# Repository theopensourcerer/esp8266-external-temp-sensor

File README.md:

# ESP8266 External Temp Sensor

This is simple board which will connect to one of those DS18B20 temperature sensors which are inside a metal sleeve and designed for external use. 

This board will ultimately live in a box outside my polytunnel with a 12V car battery, charged using solar power. One of the new features of this particular design, for me at least, is using a Switching regulator rather than a nomral LDO Linear regulator. I read that trying to drop from 12v to 3.3v is not effecient at all and can generate a lot of heat using a Linear design.

The board's software (under active testing & development) will take a measurememt, send it over MQTT and go back to sleep. I wanted this so I could compare the temperature between inside my polytunnel (see https://github.com/theopensourcerer/esp8266_envmonitor) and the normal outdoor temperature.

As with the Environment Monitor Project I plan to publish the code and a 3D case for this design. Watch this space!

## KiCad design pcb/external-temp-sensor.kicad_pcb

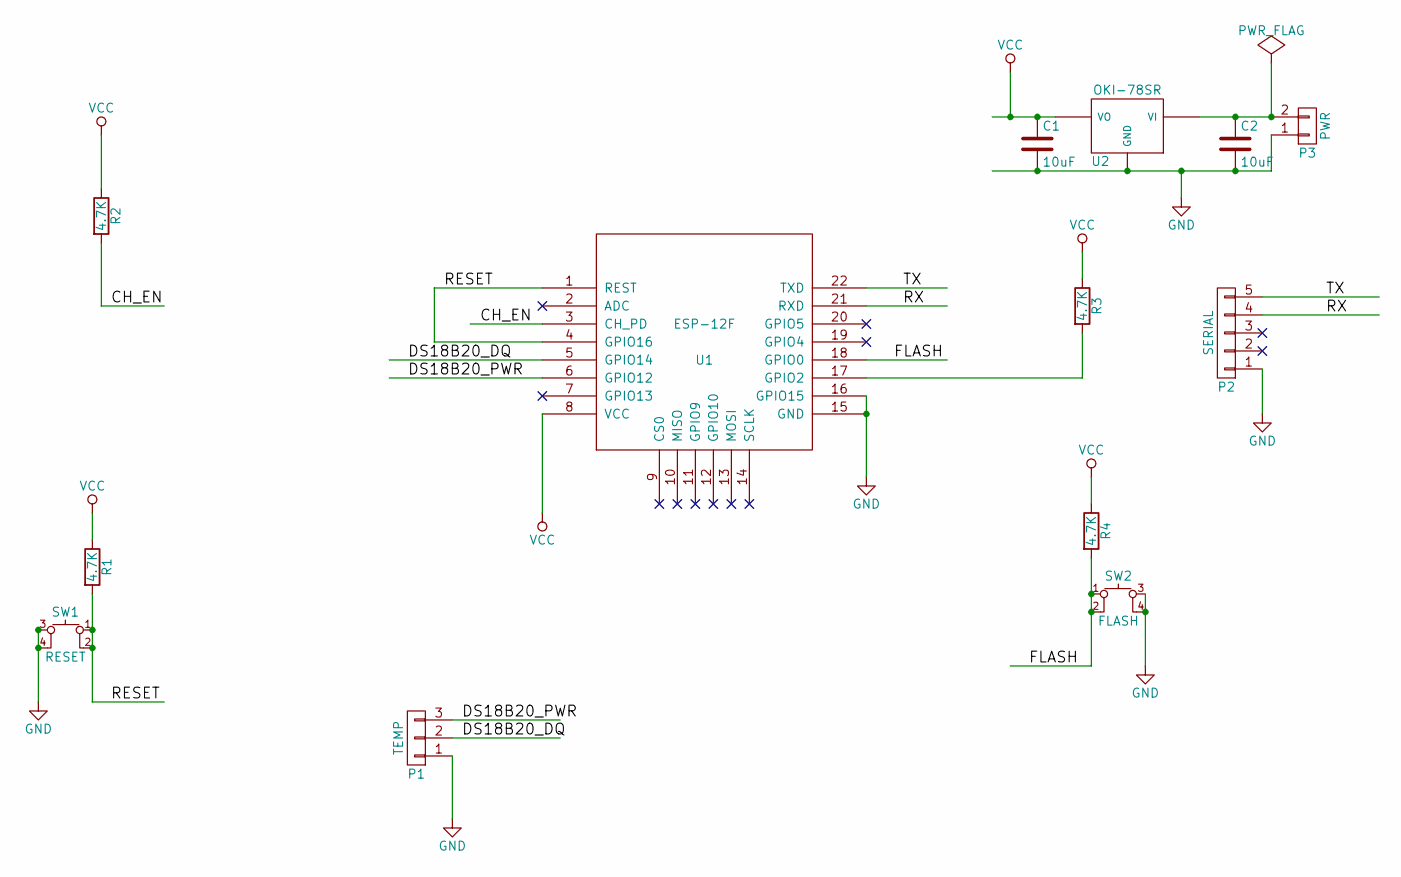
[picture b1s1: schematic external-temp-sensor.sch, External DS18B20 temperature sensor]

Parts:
C1, C2: 10uF; C_1206_HandSoldering
P1: TEMP; JST_XH_B03B-XH-A_03x2.50mm_Straight
P2: SERIAL; Pin_Header_Straight_1x05_Pitch2.54mm
P3: PWR; JST_XH_B02B-XH-A_02x2.50mm_Straight
R1, R2, R3, R4: 4.7K; R_1206_HandSoldering
SW1: RESET; SKQGAFE010_Switch
SW2: FLASH; SKQGAFE010_Switch
U1: ESP-12F; ESP-12E
U2: OKI-78SR

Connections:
/CH_EN: R2.2, U1.3 (CH_PD)
/DS18S20_DQ: P1.2, U1.5 (GPIO14)
/DS18S20_PWR: P1.3, U1.6 (GPIO12)
/FLASH: R4.2, SW2.1, SW2.2, U1.18 (GPIO0)
/RESET: R1.2, SW1.1, SW1.2, U1.1 (REST), U1.4 (GPIO16)
/RX: P2.4, U1.21 (RXD)
/TX: P2.5, U1.22 (TXD)
GND: C1.2, C2.2, P1.1, P2.1, P3.1, SW1.3, SW1.4, SW2.3, SW2.4, U1.15 (GND), U1.16 (GPIO15), U2.2 (GND)
unnamed: C2.1, P3.2, U2.1 (VI)
unnamed: R3.2, U1.17 (GPIO2)
VCC: C1.1, R1.1, R2.1, R3.1, R4.1, U1.8 (VCC), U2.3 (VO)

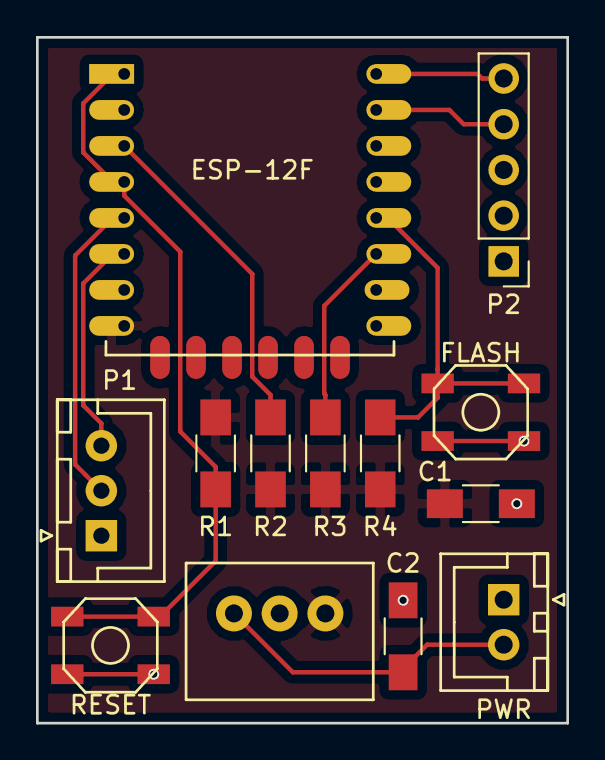
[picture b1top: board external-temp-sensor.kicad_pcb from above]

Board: 2 copper layers, 29.5 x 38.1 mm, 13 parts (0 on the bottom side), 11 nets.

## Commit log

2017-02-23 New README.md
2017-02-23 Added page and license information.
2017-02-24 Add pull-up resistor
2017-02-24 Initial commit of code
2017-02-24 Add GoTosleep if no response from DS18B20
2017-04-14 Switch to a JSON payload over MQTT and other minor changes
2017-04-14 Clean up and remove unused code

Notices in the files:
pcb/external-temp-sensor.kicad_pcb:
Solderpad Hardware License version 0.51
